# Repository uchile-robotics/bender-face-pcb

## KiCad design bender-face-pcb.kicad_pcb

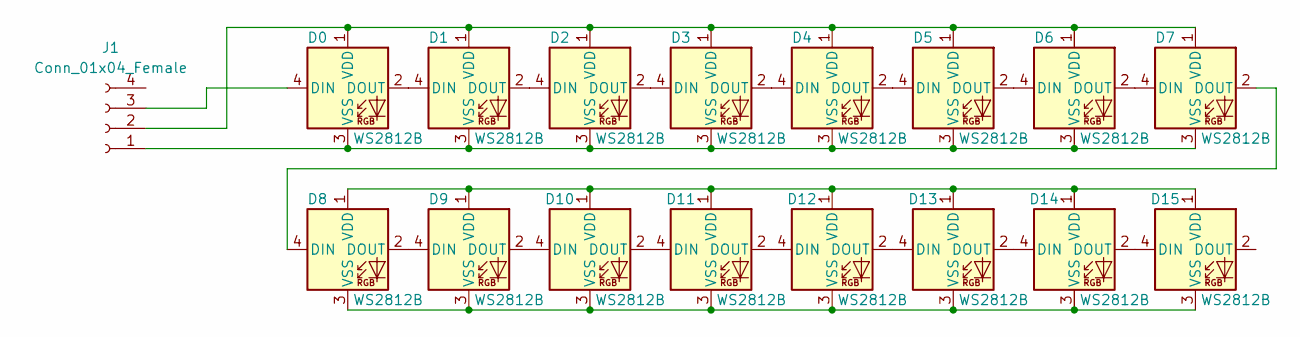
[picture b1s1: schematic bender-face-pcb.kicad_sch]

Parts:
D0, D1, D2, D3, D4, D5, D6, D7, D8, D9, D10, D11, D12, D13, D14, D15: WS2812B; LED_WS2812B_PLCC4_5.0x5.0mm_P3.2mm
J1: Conn_01x04_Female; PinSocket_1x04_P2.54mm_Vertical

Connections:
unnamed: D0.1 (VDD), D1.1 (VDD), D2.1 (VDD), D3.1 (VDD), D4.1 (VDD), D5.1 (VDD), D6.1 (VDD), D7.1 (VDD), J1.2
unnamed: D0.2 (DOUT), D1.4 (DIN)
unnamed: D0.3 (VSS), D1.3 (VSS), D2.3 (VSS), D3.3 (VSS), D4.3 (VSS), D5.3 (VSS), D6.3 (VSS), D7.3 (VSS), J1.1
unnamed: D0.4 (DIN), J1.3
unnamed: D1.2 (DOUT), D2.4 (DIN)
unnamed: D2.2 (DOUT), D3.4 (DIN)
unnamed: D3.2 (DOUT), D4.4 (DIN)
unnamed: D4.2 (DOUT), D5.4 (DIN)
unnamed: D5.2 (DOUT), D6.4 (DIN)
unnamed: D6.2 (DOUT), D7.4 (DIN)
unnamed: D7.2 (DOUT), D8.4 (DIN)
unnamed: D8.1 (VDD), D9.1 (VDD), D10.1 (VDD), D11.1 (VDD), D12.1 (VDD), D13.1 (VDD), D14.1 (VDD), D15.1 (VDD)
unnamed: D9.2 (DOUT), D10.4 (DIN)
unnamed: D8.3 (VSS), D9.3 (VSS), D10.3 (VSS), D11.3 (VSS), D12.3 (VSS), D13.3 (VSS), D14.3 (VSS), D15.3 (VSS)
unnamed: D8.2 (DOUT), D9.4 (DIN)
unnamed: D10.2 (DOUT), D11.4 (DIN)
unnamed: D11.2 (DOUT), D12.4 (DIN)
unnamed: D12.2 (DOUT), D13.4 (DIN)
unnamed: D13.2 (DOUT), D14.4 (DIN)
unnamed: D14.2 (DOUT), D15.4 (DIN)

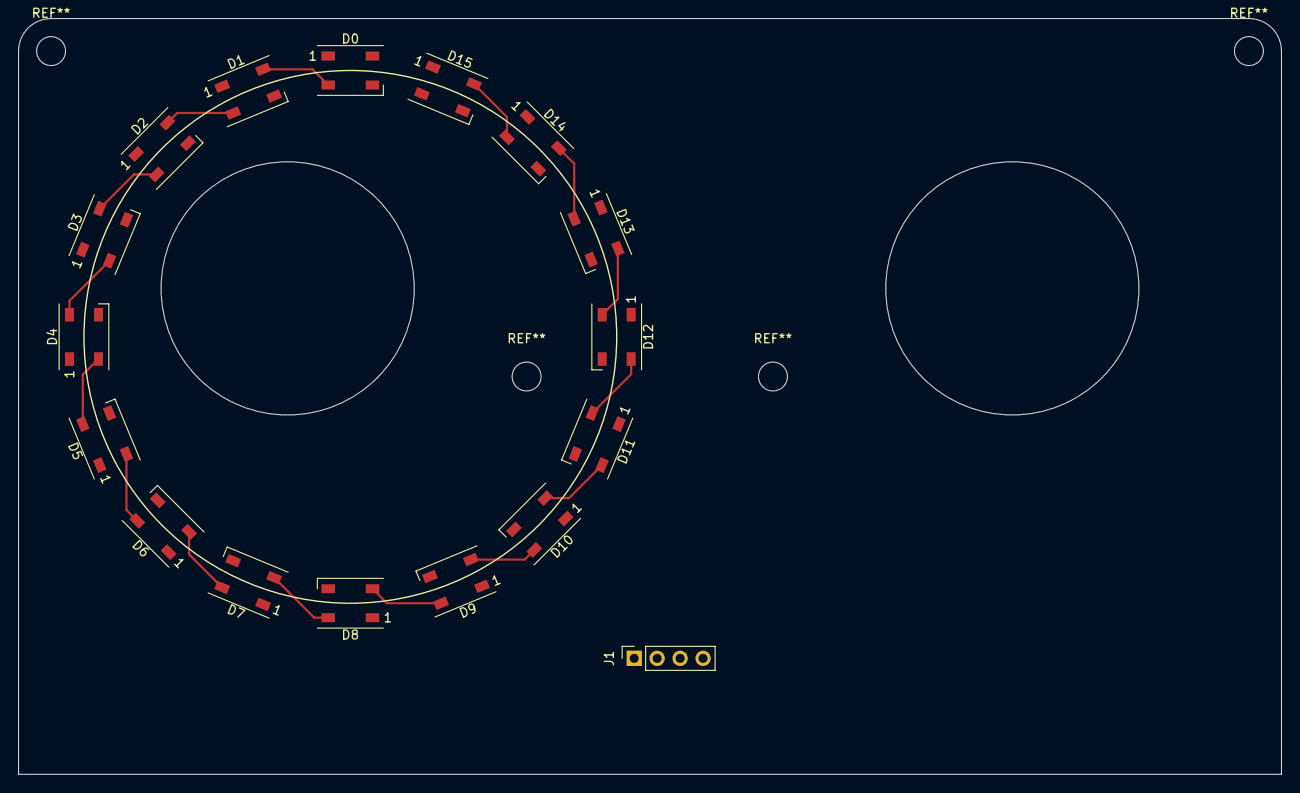
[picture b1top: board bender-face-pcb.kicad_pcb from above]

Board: 2 copper layers, 139.7 x 83.6 mm, 17 parts (0 on the bottom side), 20 nets.

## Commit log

2022-04-22 Initialize project
2022-04-22 Testing metrics for the PCB on the Board File
2022-09-20 added completed eagle version
